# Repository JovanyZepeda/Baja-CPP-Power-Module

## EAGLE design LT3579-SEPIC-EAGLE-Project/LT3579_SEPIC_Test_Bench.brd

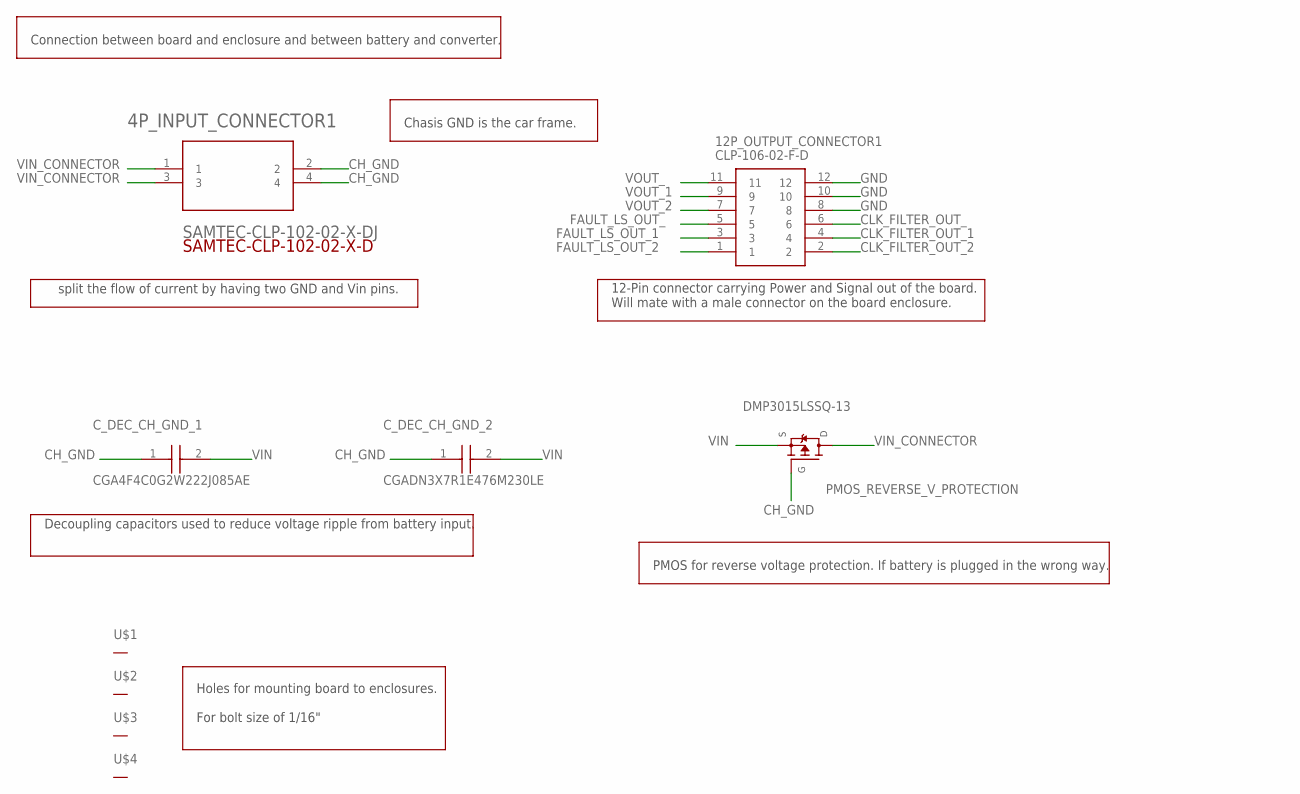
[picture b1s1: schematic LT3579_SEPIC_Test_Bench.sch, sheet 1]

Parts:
4P_INPUT_CONNECTOR1: SAMTEC-CLP-102-02-X-DJ; SAMTEC-CLP-102-02-X-D
12P_OUTPUT_CONNECTOR1: CLP-106-02-F-D; CLP-106-02-XXX
C_DEC_CH_GND_1: CGA4F4C0G2W222J085AE; CAPC2012X100N
C_DEC_CH_GND_2: CGADN3X7R1E476M230LE; CAPC7563X250N
PMOS_REVERSE_V_PROTECTION: DMP3015LSSQ-13; SOIC127P600X170-8N
U$1, U$2, U$3, U$4: THROUGH_HOLE_; THROUGH_HOLE

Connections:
CH_GND: 4P_INPUT_CONNECTOR1.2, 4P_INPUT_CONNECTOR1.4, C_DEC_CH_GND_1.1, C_DEC_CH_GND_2.1, PMOS_REVERSE_V_PROTECTION.4 (G1); also elsewhere on the board
CLK_FILTER_OUT_: 12P_OUTPUT_CONNECTOR1.6; also elsewhere on the board
CLK_FILTER_OUT_1: 12P_OUTPUT_CONNECTOR1.4; also elsewhere on the board
CLK_FILTER_OUT_2: 12P_OUTPUT_CONNECTOR1.2; also elsewhere on the board
FAULT_LS_OUT_: 12P_OUTPUT_CONNECTOR1.5; also elsewhere on the board
FAULT_LS_OUT_1: 12P_OUTPUT_CONNECTOR1.3; also elsewhere on the board
FAULT_LS_OUT_2: 12P_OUTPUT_CONNECTOR1.1; also elsewhere on the board
GND: 12P_OUTPUT_CONNECTOR1.8, 12P_OUTPUT_CONNECTOR1.10, 12P_OUTPUT_CONNECTOR1.12; also elsewhere on the board
VIN: C_DEC_CH_GND_1.2, C_DEC_CH_GND_2.2, PMOS_REVERSE_V_PROTECTION.1 (S1), PMOS_REVERSE_V_PROTECTION.2 (S1), PMOS_REVERSE_V_PROTECTION.3 (S1); also elsewhere on the board
VIN_CONNECTOR: 4P_INPUT_CONNECTOR1.1, 4P_INPUT_CONNECTOR1.3, PMOS_REVERSE_V_PROTECTION.5 (D1), PMOS_REVERSE_V_PROTECTION.6 (D1), PMOS_REVERSE_V_PROTECTION.7 (D1), PMOS_REVERSE_V_PROTECTION.8 (D1)
VOUT_: 12P_OUTPUT_CONNECTOR1.11; also elsewhere on the board
VOUT_1: 12P_OUTPUT_CONNECTOR1.9; also elsewhere on the board
VOUT_2: 12P_OUTPUT_CONNECTOR1.7; also elsewhere on the board

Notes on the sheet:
Connection between board and enclosure and between battery and converter.
split the flow of current by having two GND and Vin pins.
12-Pin connector carrying Power and Signal out of the board. Will mate with a male connector on the board enclosure.
Decoupling capacitors used to reduce voltage ripple from battery input.
PMOS for reverse voltage protection. If battery is plugged in the wrong way.
Chasis GND is the car frame.
Holes for mounting board to enclosures. For bolt size of 1/16"

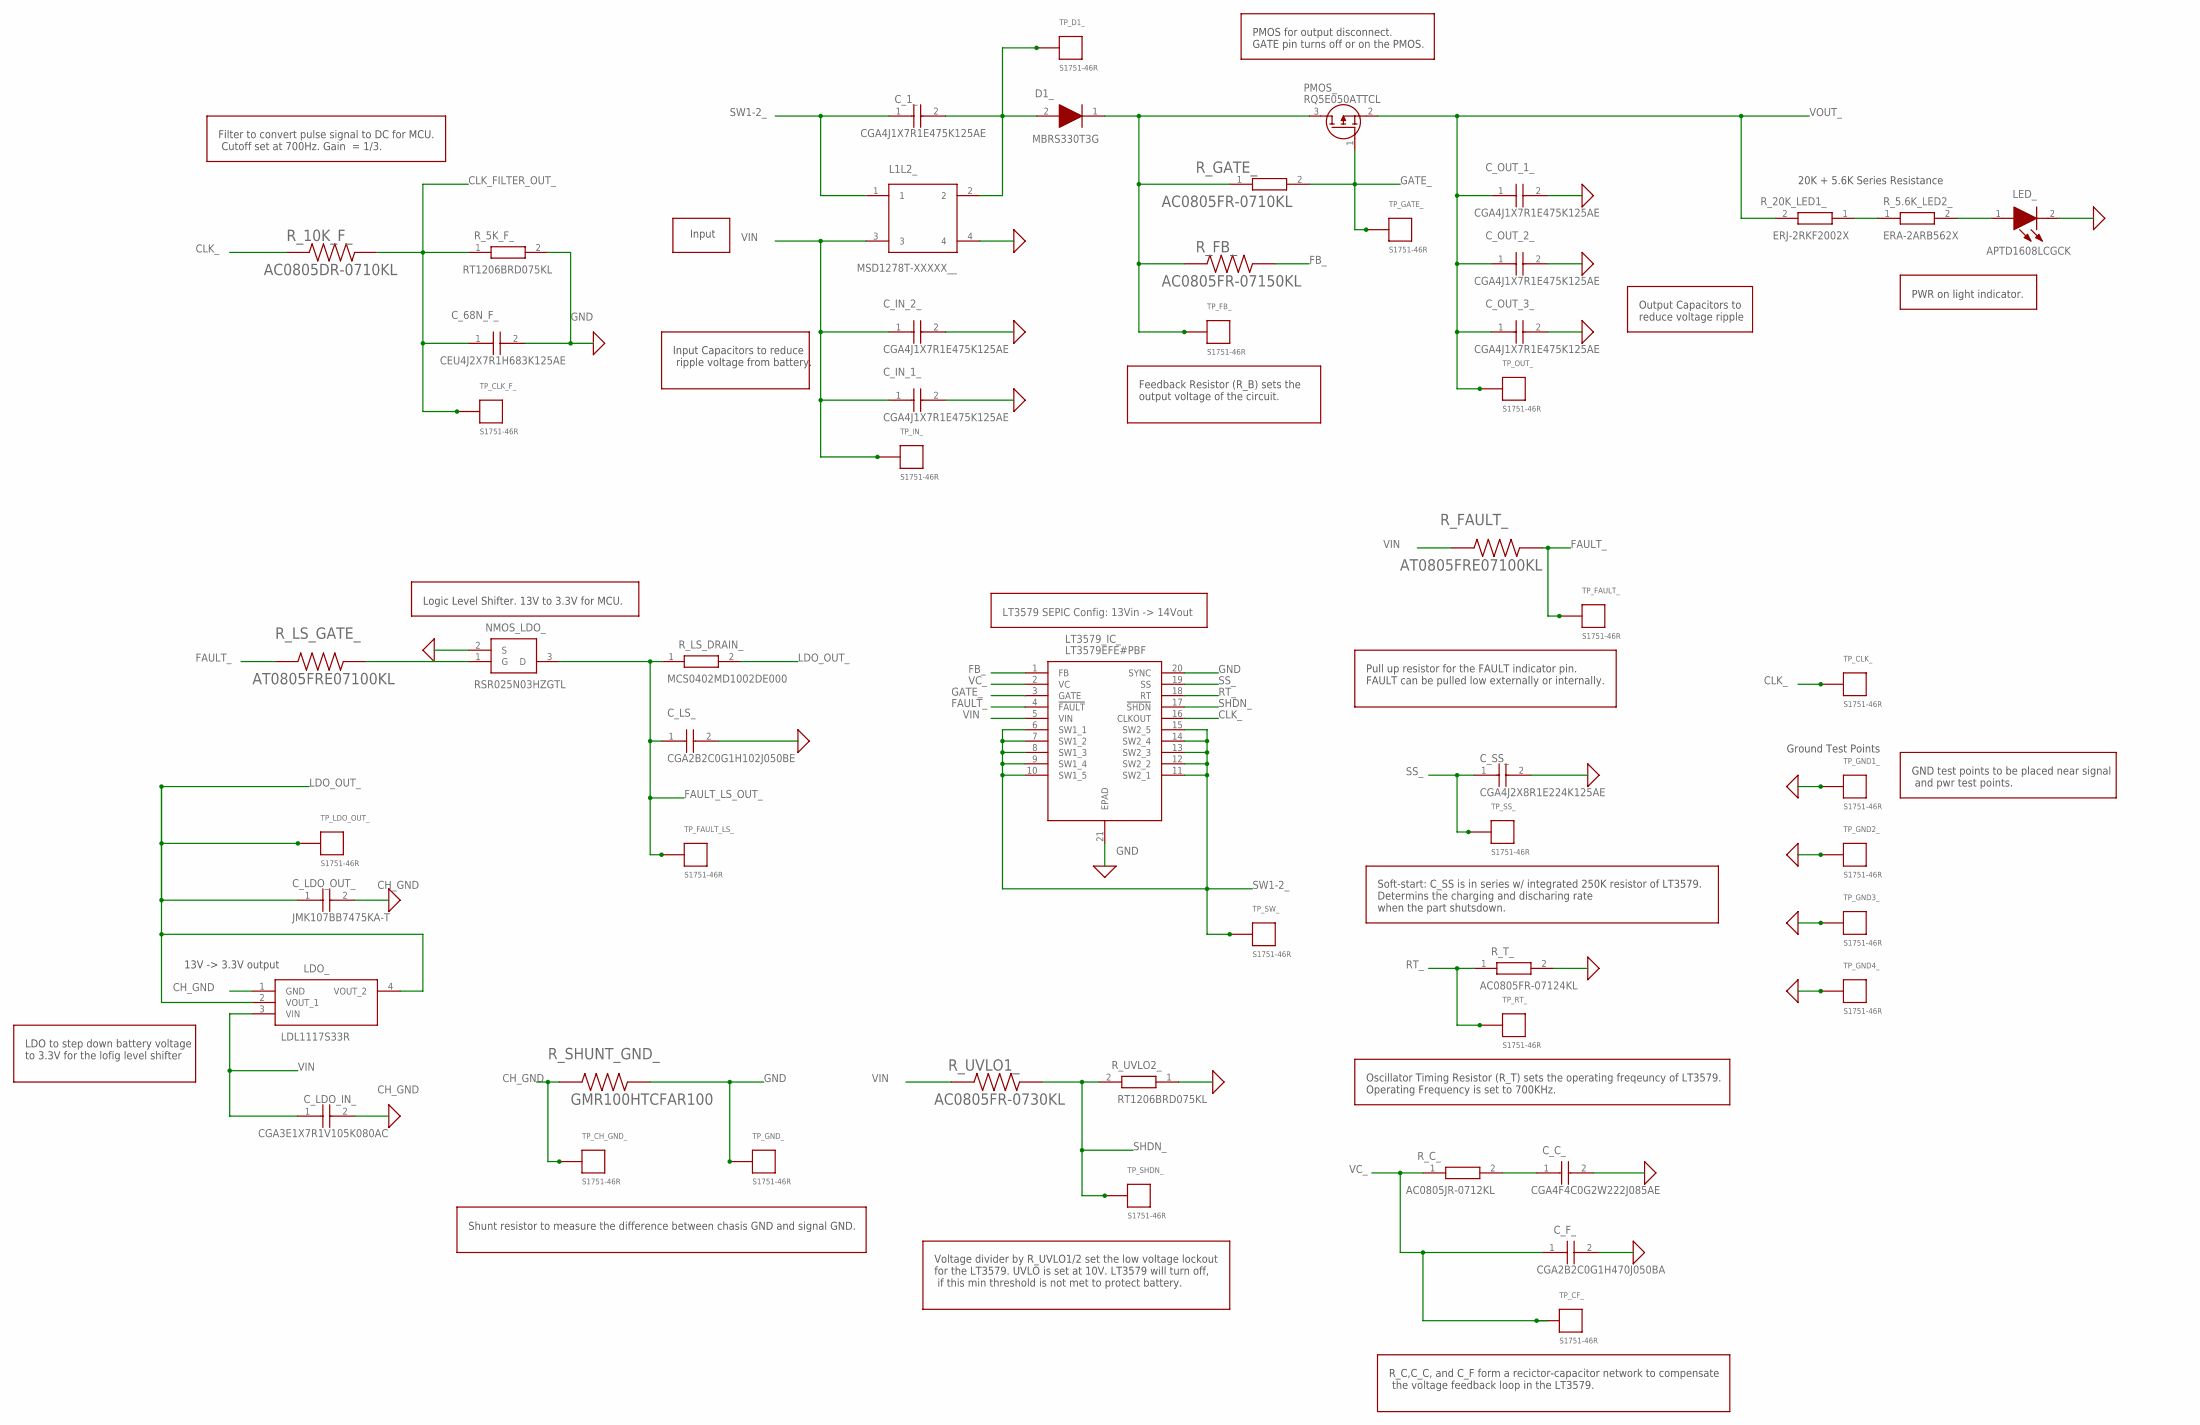
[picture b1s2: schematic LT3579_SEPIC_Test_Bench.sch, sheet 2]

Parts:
C_1_: CGA4J1X7R1E475K125AE; CAPC2012X145N
C_68N_F_: CEU4J2X7R1H683K125AE; CAPC2013X150N
C_C_: CGA4F4C0G2W222J085AE; CAPC2012X100N
C_F_: CGA2B2C0G1H470J050BA; CAPC1005X55N
C_IN_1_, C_IN_2_: CGA4J1X7R1E475K125AE; CAPC2012X145N
C_LDO_IN_: CGA3E1X7R1V105K080AC; CAPC1608X90N
C_LDO_OUT_: JMK107BB7475KA-T; CAPC1608X90N
C_LS_: CGA2B2C0G1H102J050BE; CAPC1005X55N
C_OUT_1_, C_OUT_2_, C_OUT_3_: CGA4J1X7R1E475K125AE; CAPC2012X145N
C_SS_: CGA4J2X8R1E224K125AE; CAPC2012X145N
D1_: MBRS330T3G; DIOM7958X256N
L1L2_: MSD1278T-XXXXX__; MSD1278T-822MLXX
LDO_: LDL1117S33R; SOT230P700X180-4N
LED_: APTD1608LCGCK; APT1608CGCK
LT3579_IC_: LT3579EFE#PBF; SOP65P640X120-21N
NMOS_LDO_: RSR025N03HZGTL; SOT95P280X100-3N
PMOS_: RQ5E050ATTCL; SOT95P280X100-3N
R_5.6K_LED2_: ERA-2ARB562X; ERA2AED122X
R_5K_F_: RT1206BRD075KL; RESC3116X65N
R_10K_F_: AC0805DR-0710KL; RESC2012X60N
R_20K_LED1_: ERJ-2RKF2002X; ERJ2R_(0402)
R_C_: AC0805JR-0712KL; RESC2012X60N
R_FAULT_: AT0805FRE07100KL; RESC2012X60N
R_FB_: AC0805FR-07150KL; RESC2012X60N
R_GATE_: AC0805FR-0710KL; RESC2012X60N
R_LS_DRAIN_: MCS0402MD1002DE000; RESC1005X37N
R_LS_GATE_: AT0805FRE07100KL; RESC2012X60N
R_SHUNT_GND_: GMR100HTCFAR100; RESC6432X55N
R_T_: AC0805FR-07124KL; RESC2012X60N
R_UVLO1_: AC0805FR-0730KL; RESC2012X60N
R_UVLO2_: RT1206BRD075KL; RESC3116X65N
TP_CF_: S1751-46R; S1751-46R_
TP_CH_GND_: S1751-46R; S1751-46R_
TP_CLK_: S1751-46R; S1751-46R_
TP_CLK_F_: S1751-46R; S1751-46R_
TP_D1_: S1751-46R; S1751-46R_
TP_FAULT_: S1751-46R; S1751-46R_
TP_FAULT_LS_: S1751-46R; S1751-46R_
TP_FB_: S1751-46R; S1751-46R_
TP_GATE_: S1751-46R; S1751-46R_
TP_GND1_, TP_GND2_, TP_GND3_, TP_GND4_: S1751-46R; S1751-46R_
TP_GND_: S1751-46R; S1751-46R_
TP_IN_: S1751-46R; S1751-46R_
TP_LDO_OUT_: S1751-46R; S1751-46R_
TP_OUT_: S1751-46R; S1751-46R_
TP_RT_: S1751-46R; S1751-46R_
TP_SHDN_: S1751-46R; S1751-46R_
TP_SS_: S1751-46R; S1751-46R_
TP_SW_: S1751-46R; S1751-46R_

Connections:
CH_GND: C_LDO_IN_.2, C_LDO_OUT_.2, LDO_.1 (GND), R_SHUNT_GND_.1, TP_CH_GND_.1; also elsewhere on the board
CLK_: LT3579_IC_.16 (CLKOUT), R_10K_F_.1, TP_CLK_.1
CLK_FILTER_OUT_: C_68N_F_.1, R_5K_F_.1, R_10K_F_.2, TP_CLK_F_.1; also elsewhere on the board
FAULT_: LT3579_IC_.4 (!FAULT), R_FAULT_.1, R_LS_GATE_.1, TP_FAULT_.1
FAULT_LS_OUT_: C_LS_.1, NMOS_LDO_.3 (D), R_LS_DRAIN_.1, TP_FAULT_LS_.1; also elsewhere on the board
FB_: LT3579_IC_.1 (FB), R_FB_.2
GATE_: LT3579_IC_.3 (GATE), PMOS_.1 (G), R_GATE_.2, TP_GATE_.1
GND: C_68N_F_.2, C_C_.2, C_F_.2, C_IN_1_.2, C_IN_2_.2, C_LS_.2, C_OUT_1_.2, C_OUT_2_.2, C_OUT_3_.2, C_SS_.2, L1L2_.4, LED_.2 (K), LT3579_IC_.20 (SYNC), LT3579_IC_.21 (EPAD), NMOS_LDO_.2 (S), R_5K_F_.2, R_SHUNT_GND_.2, R_T_.2, R_UVLO2_.1, TP_GND1_.1, TP_GND2_.1, TP_GND3_.1, TP_GND4_.1, TP_GND_.1; also elsewhere on the board
LDO_OUT_: C_LDO_OUT_.1, LDO_.2 (VOUT_1), LDO_.4 (VOUT_2), R_LS_DRAIN_.2, TP_LDO_OUT_.1; also elsewhere on the board
unnamed: C_C_.1, R_C_.2
unnamed: NMOS_LDO_.1 (G), R_LS_GATE_.2
unnamed: C_1_.2, D1_.2 (A), L1L2_.2, TP_D1_.1
unnamed: R_5.6K_LED2_.1, R_20K_LED1_.1
unnamed: D1_.1 (K), PMOS_.3 (D), R_FB_.1, R_GATE_.1, TP_FB_.1
unnamed: LED_.1 (A), R_5.6K_LED2_.2
RT_: LT3579_IC_.18 (RT), R_T_.1, TP_RT_.1
SHDN_: LT3579_IC_.17 (!SHDN), R_UVLO1_.1, R_UVLO2_.2, TP_SHDN_.1
SS_: C_SS_.1, LT3579_IC_.19 (SS), TP_SS_.1
SW1-2_: C_1_.1, L1L2_.1, LT3579_IC_.6 (SW1_1), LT3579_IC_.7 (SW1_2), LT3579_IC_.8 (SW1_3), LT3579_IC_.9 (SW1_4), LT3579_IC_.10 (SW1_5), LT3579_IC_.11 (SW2_1), LT3579_IC_.12 (SW2_2), LT3579_IC_.13 (SW2_3), LT3579_IC_.14 (SW2_4), LT3579_IC_.15 (SW2_5), TP_SW_.1
VC_: C_F_.1, LT3579_IC_.2 (VC), R_C_.1, TP_CF_.1
VIN: C_IN_1_.1, C_IN_2_.1, C_LDO_IN_.1, L1L2_.3, LDO_.3 (VIN), LT3579_IC_.5 (VIN), R_FAULT_.2, R_UVLO1_.2, TP_IN_.1; also elsewhere on the board
VOUT_: C_OUT_1_.1, C_OUT_2_.1, C_OUT_3_.1, PMOS_.2 (S), R_20K_LED1_.2, TP_OUT_.1; also elsewhere on the board

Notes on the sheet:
LT3579 SEPIC Config: 13Vin -> 14Vout
Ground Test Points
Filter to convert pulse signal to DC for MCU. Cutoff set at 700Hz. Gain = 1/3.
13V -> 3.3V output
Logic Level Shifter. 13V to 3.3V for MCU.
20K + 5.6K Series Resistance
PWR on light indicator.
Voltage divider by R_UVLO1/2 set the low voltage lockout for the LT3579. UVLO is set at 10V. LT3579 will turn off, if this min threshold is not met to protect battery.
Oscillator Timing Resistor (R_T) sets the operating freqeuncy of LT3579. Operating Frequency is set to 700KHz.
R_C,C_C, and C_F form a recictor-capacitor network to compensate the voltage feedback loop in the LT3579.
Soft-start: C_SS is in series w/ integrated 250K resistor of LT3579. Determins the charging and discharing rate when the part shutsdown.
Pull up resistor for the FAULT indicator pin. FAULT can be pulled low externally or internally.
Shunt resistor to measure the difference between chasis GND and signal GND.
LDO to step down battery voltage to 3.3V for the lofig level shifter
GND test points to be placed near signal and pwr test points.
Input Capacitors to reduce ripple voltage from battery.
Output Capacitors to reduce voltage ripple
PMOS for output disconnect. GATE pin turns off or on the PMOS.
Feedback Resistor (R_B) sets the output voltage of the circuit.
Input

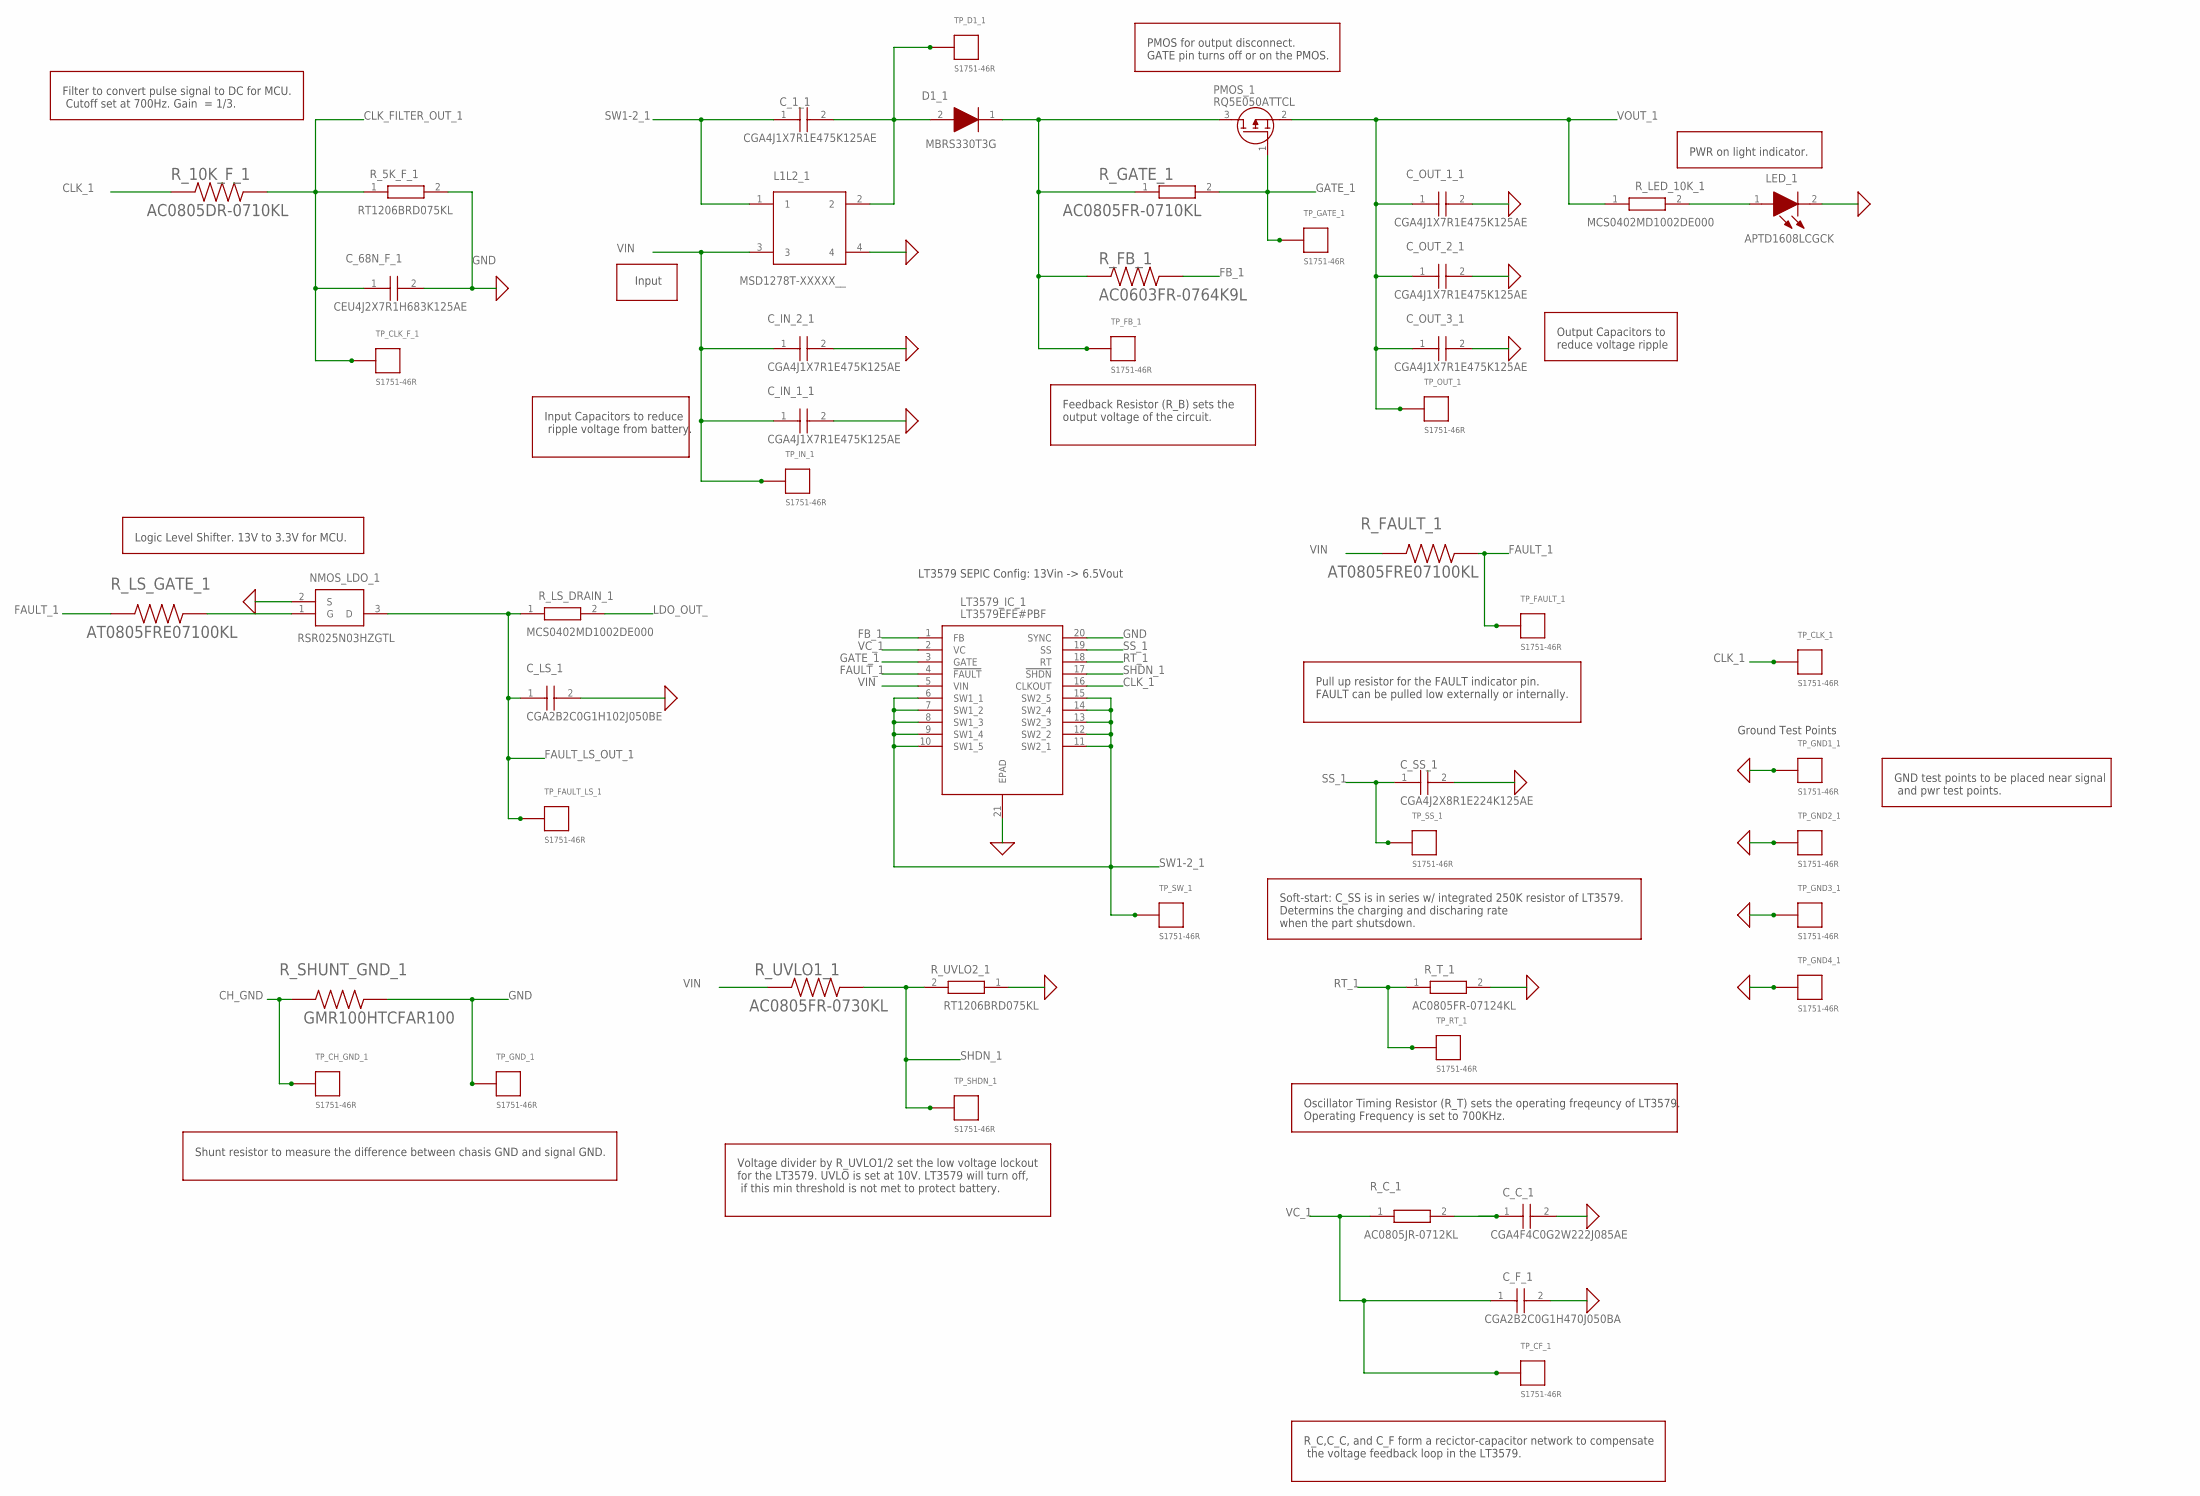
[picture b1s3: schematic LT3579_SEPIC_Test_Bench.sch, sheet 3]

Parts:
C_1_1: CGA4J1X7R1E475K125AE; CAPC2012X145N
C_68N_F_1: CEU4J2X7R1H683K125AE; CAPC2013X150N
C_C_1: CGA4F4C0G2W222J085AE; CAPC2012X100N
C_F_1: CGA2B2C0G1H470J050BA; CAPC1005X55N
C_IN_1_1, C_IN_2_1: CGA4J1X7R1E475K125AE; CAPC2012X145N
C_LS_1: CGA2B2C0G1H102J050BE; CAPC1005X55N
C_OUT_1_1, C_OUT_2_1, C_OUT_3_1: CGA4J1X7R1E475K125AE; CAPC2012X145N
C_SS_1: CGA4J2X8R1E224K125AE; CAPC2012X145N
D1_1: MBRS330T3G; DIOM7958X256N
L1L2_1: MSD1278T-XXXXX__; MSD1278T-822MLXX
LED_1: APTD1608LCGCK; APT1608CGCK
LT3579_IC_1: LT3579EFE#PBF; SOP65P640X120-21N
NMOS_LDO_1: RSR025N03HZGTL; SOT95P280X100-3N
PMOS_1: RQ5E050ATTCL; SOT95P280X100-3N
R_5K_F_1: RT1206BRD075KL; RESC3116X65N
R_10K_F_1: AC0805DR-0710KL; RESC2012X60N
R_C_1: AC0805JR-0712KL; RESC2012X60N
R_FAULT_1: AT0805FRE07100KL; RESC2012X60N
R_FB_1: AC0603FR-0764K9L; RESC1608X55N
R_GATE_1: AC0805FR-0710KL; RESC2012X60N
R_LED_10K_1: MCS0402MD1002DE000; RESC1005X37N
R_LS_DRAIN_1: MCS0402MD1002DE000; RESC1005X37N
R_LS_GATE_1: AT0805FRE07100KL; RESC2012X60N
R_SHUNT_GND_1: GMR100HTCFAR100; RESC6432X55N
R_T_1: AC0805FR-07124KL; RESC2012X60N
R_UVLO1_1: AC0805FR-0730KL; RESC2012X60N
R_UVLO2_1: RT1206BRD075KL; RESC3116X65N
TP_CF_1: S1751-46R; S1751-46R_
TP_CH_GND_1: S1751-46R; S1751-46R_
TP_CLK_1: S1751-46R; S1751-46R_
TP_CLK_F_1: S1751-46R; S1751-46R_
TP_D1_1: S1751-46R; S1751-46R_
TP_FAULT_1: S1751-46R; S1751-46R_
TP_FAULT_LS_1: S1751-46R; S1751-46R_
TP_FB_1: S1751-46R; S1751-46R_
TP_GATE_1: S1751-46R; S1751-46R_
TP_GND1_1, TP_GND2_1, TP_GND3_1, TP_GND4_1: S1751-46R; S1751-46R_
TP_GND_1: S1751-46R; S1751-46R_
TP_IN_1: S1751-46R; S1751-46R_
TP_OUT_1: S1751-46R; S1751-46R_
TP_RT_1: S1751-46R; S1751-46R_
TP_SHDN_1: S1751-46R; S1751-46R_
TP_SS_1: S1751-46R; S1751-46R_
TP_SW_1: S1751-46R; S1751-46R_

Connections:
CH_GND: R_SHUNT_GND_1.1, TP_CH_GND_1.1; also elsewhere on the board
CLK_1: LT3579_IC_1.16 (CLKOUT), R_10K_F_1.1, TP_CLK_1.1
CLK_FILTER_OUT_1: C_68N_F_1.1, R_5K_F_1.1, R_10K_F_1.2, TP_CLK_F_1.1; also elsewhere on the board
FAULT_1: LT3579_IC_1.4 (!FAULT), R_FAULT_1.1, R_LS_GATE_1.1, TP_FAULT_1.1
FAULT_LS_OUT_1: C_LS_1.1, NMOS_LDO_1.3 (D), R_LS_DRAIN_1.1, TP_FAULT_LS_1.1; also elsewhere on the board
FB_1: LT3579_IC_1.1 (FB), R_FB_1.2
GATE_1: LT3579_IC_1.3 (GATE), PMOS_1.1 (G), R_GATE_1.2, TP_GATE_1.1
GND: C_68N_F_1.2, C_C_1.2, C_F_1.2, C_IN_1_1.2, C_IN_2_1.2, C_LS_1.2, C_OUT_1_1.2, C_OUT_2_1.2, C_OUT_3_1.2, C_SS_1.2, L1L2_1.4, LED_1.2 (K), LT3579_IC_1.20 (SYNC), LT3579_IC_1.21 (EPAD), NMOS_LDO_1.2 (S), R_5K_F_1.2, R_SHUNT_GND_1.2, R_T_1.2, R_UVLO2_1.1, TP_GND1_1.1, TP_GND2_1.1, TP_GND3_1.1, TP_GND4_1.1, TP_GND_1.1; also elsewhere on the board
LDO_OUT_: R_LS_DRAIN_1.2; also elsewhere on the board
unnamed: C_1_1.2, D1_1.2 (A), L1L2_1.2, TP_D1_1.1
unnamed: C_C_1.1, R_C_1.2
unnamed: D1_1.1 (K), PMOS_1.3 (D), R_FB_1.1, R_GATE_1.1, TP_FB_1.1
unnamed: NMOS_LDO_1.1 (G), R_LS_GATE_1.2
unnamed: LED_1.1 (A), R_LED_10K_1.2
RT_1: LT3579_IC_1.18 (RT), R_T_1.1, TP_RT_1.1
SHDN_1: LT3579_IC_1.17 (!SHDN), R_UVLO1_1.1, R_UVLO2_1.2, TP_SHDN_1.1
SS_1: C_SS_1.1, LT3579_IC_1.19 (SS), TP_SS_1.1
SW1-2_1: C_1_1.1, L1L2_1.1, LT3579_IC_1.6 (SW1_1), LT3579_IC_1.7 (SW1_2), LT3579_IC_1.8 (SW1_3), LT3579_IC_1.9 (SW1_4), LT3579_IC_1.10 (SW1_5), LT3579_IC_1.11 (SW2_1), LT3579_IC_1.12 (SW2_2), LT3579_IC_1.13 (SW2_3), LT3579_IC_1.14 (SW2_4), LT3579_IC_1.15 (SW2_5), TP_SW_1.1
VC_1: C_F_1.1, LT3579_IC_1.2 (VC), R_C_1.1, TP_CF_1.1
VIN: C_IN_1_1.1, C_IN_2_1.1, L1L2_1.3, LT3579_IC_1.5 (VIN), R_FAULT_1.2, R_UVLO1_1.2, TP_IN_1.1; also elsewhere on the board
VOUT_1: C_OUT_1_1.1, C_OUT_2_1.1, C_OUT_3_1.1, PMOS_1.2 (S), R_LED_10K_1.1, TP_OUT_1.1; also elsewhere on the board

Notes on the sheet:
LT3579 SEPIC Config: 13Vin -> 6.5Vout
Ground Test Points
Filter to convert pulse signal to DC for MCU. Cutoff set at 700Hz. Gain = 1/3.
Logic Level Shifter. 13V to 3.3V for MCU.
Voltage divider by R_UVLO1/2 set the low voltage lockout for the LT3579. UVLO is set at 10V. LT3579 will turn off, if this min threshold is not met to protect battery.
R_C,C_C, and C_F form a recictor-capacitor network to compensate the voltage feedback loop in the LT3579.
Oscillator Timing Resistor (R_T) sets the operating freqeuncy of LT3579. Operating Frequency is set to 700KHz.
Soft-start: C_SS is in series w/ integrated 250K resistor of LT3579. Determins the charging and discharing rate when the part shutsdown.
GND test points to be placed near signal and pwr test points.
Pull up resistor for the FAULT indicator pin. FAULT can be pulled low externally or internally.
PWR on light indicator.
Output Capacitors to reduce voltage ripple
Feedback Resistor (R_B) sets the output voltage of the circuit.
PMOS for output disconnect. GATE pin turns off or on the PMOS.
Input Capacitors to reduce ripple voltage from battery.
Input
Shunt resistor to measure the difference between chasis GND and signal GND.

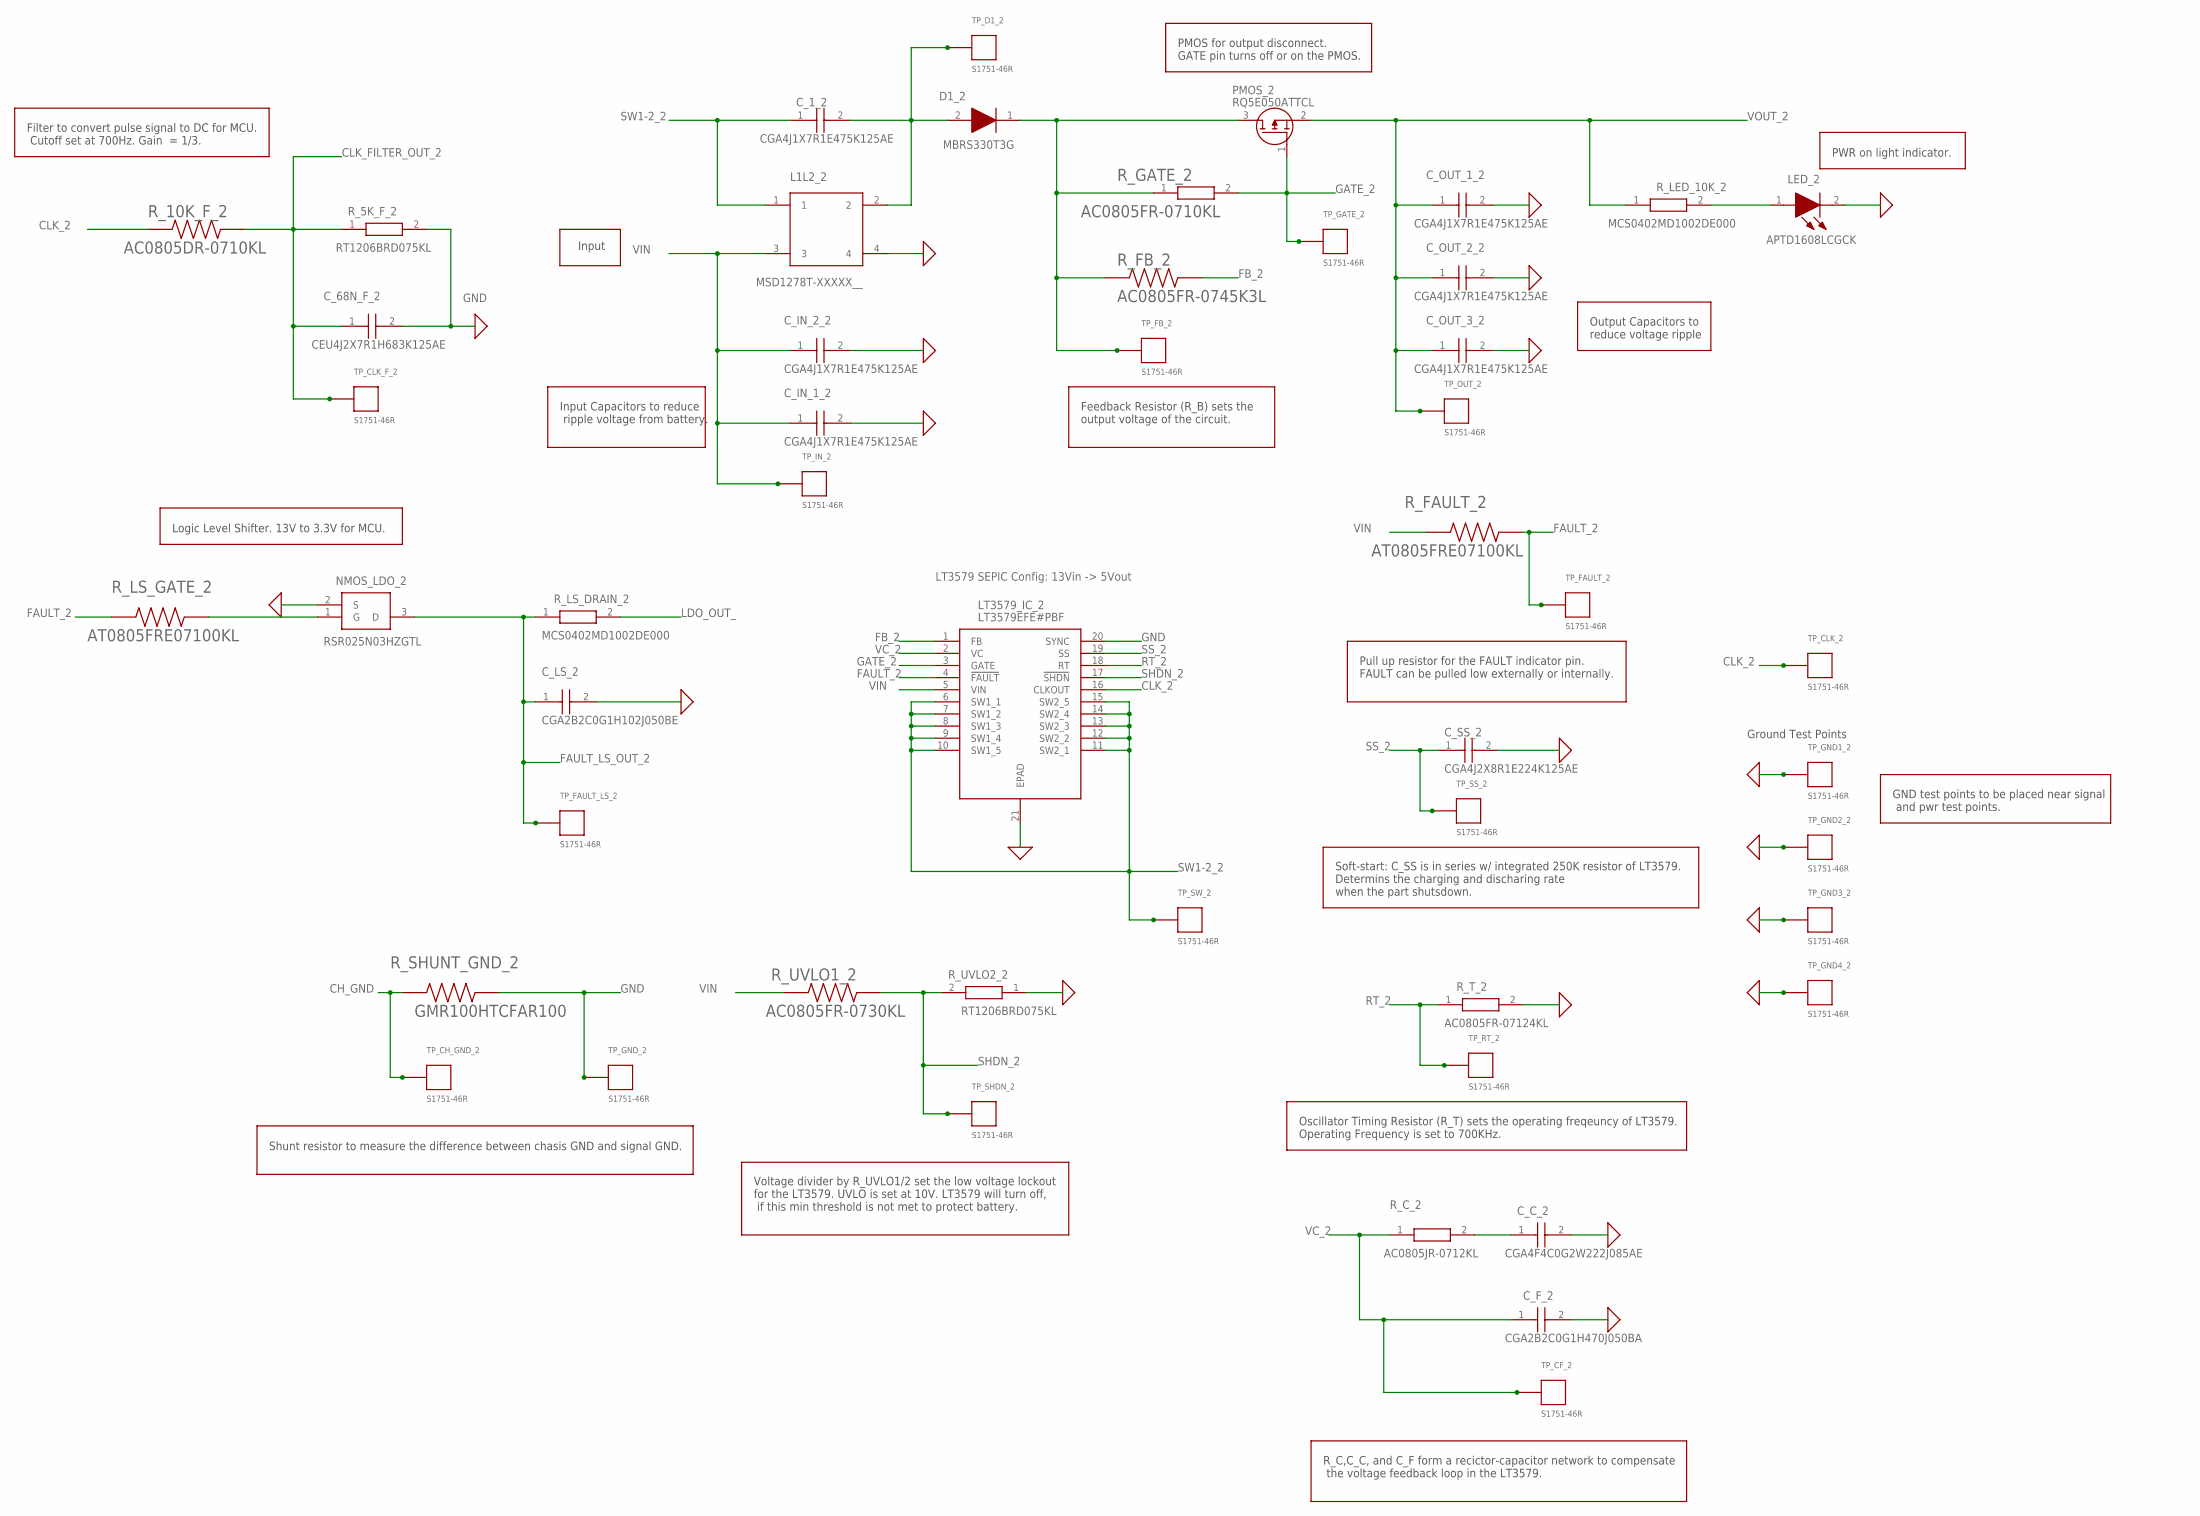
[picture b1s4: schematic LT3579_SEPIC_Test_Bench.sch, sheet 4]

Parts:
C_1_2: CGA4J1X7R1E475K125AE; CAPC2012X145N
C_68N_F_2: CEU4J2X7R1H683K125AE; CAPC2013X150N
C_C_2: CGA4F4C0G2W222J085AE; CAPC2012X100N
C_F_2: CGA2B2C0G1H470J050BA; CAPC1005X55N
C_IN_1_2, C_IN_2_2: CGA4J1X7R1E475K125AE; CAPC2012X145N
C_LS_2: CGA2B2C0G1H102J050BE; CAPC1005X55N
C_OUT_1_2, C_OUT_2_2, C_OUT_3_2: CGA4J1X7R1E475K125AE; CAPC2012X145N
C_SS_2: CGA4J2X8R1E224K125AE; CAPC2012X145N
D1_2: MBRS330T3G; DIOM7958X256N
L1L2_2: MSD1278T-XXXXX__; MSD1278T-822MLXX
LED_2: APTD1608LCGCK; APT1608CGCK
LT3579_IC_2: LT3579EFE#PBF; SOP65P640X120-21N
NMOS_LDO_2: RSR025N03HZGTL; SOT95P280X100-3N
PMOS_2: RQ5E050ATTCL; SOT95P280X100-3N
R_5K_F_2: RT1206BRD075KL; RESC3116X65N
R_10K_F_2: AC0805DR-0710KL; RESC2012X60N
R_C_2: AC0805JR-0712KL; RESC2012X60N
R_FAULT_2: AT0805FRE07100KL; RESC2012X60N
R_FB_2: AC0805FR-0745K3L; RESC2012X60N
R_GATE_2: AC0805FR-0710KL; RESC2012X60N
R_LED_10K_2: MCS0402MD1002DE000; RESC1005X37N
R_LS_DRAIN_2: MCS0402MD1002DE000; RESC1005X37N
R_LS_GATE_2: AT0805FRE07100KL; RESC2012X60N
R_SHUNT_GND_2: GMR100HTCFAR100; RESC6432X55N
R_T_2: AC0805FR-07124KL; RESC2012X60N
R_UVLO1_2: AC0805FR-0730KL; RESC2012X60N
R_UVLO2_2: RT1206BRD075KL; RESC3116X65N
TP_CF_2: S1751-46R; S1751-46R_
TP_CH_GND_2: S1751-46R; S1751-46R_
TP_CLK_2: S1751-46R; S1751-46R_
TP_CLK_F_2: S1751-46R; S1751-46R_
TP_D1_2: S1751-46R; S1751-46R_
TP_FAULT_2: S1751-46R; S1751-46R_
TP_FAULT_LS_2: S1751-46R; S1751-46R_
TP_FB_2: S1751-46R; S1751-46R_
TP_GATE_2: S1751-46R; S1751-46R_
TP_GND1_2, TP_GND2_2, TP_GND3_2, TP_GND4_2: S1751-46R; S1751-46R_
TP_GND_2: S1751-46R; S1751-46R_
TP_IN_2: S1751-46R; S1751-46R_
TP_OUT_2: S1751-46R; S1751-46R_
TP_RT_2: S1751-46R; S1751-46R_
TP_SHDN_2: S1751-46R; S1751-46R_
TP_SS_2: S1751-46R; S1751-46R_
TP_SW_2: S1751-46R; S1751-46R_

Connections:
CH_GND: R_SHUNT_GND_2.1, TP_CH_GND_2.1; also elsewhere on the board
CLK_2: LT3579_IC_2.16 (CLKOUT), R_10K_F_2.1, TP_CLK_2.1
CLK_FILTER_OUT_2: C_68N_F_2.1, R_5K_F_2.1, R_10K_F_2.2, TP_CLK_F_2.1; also elsewhere on the board
FAULT_2: LT3579_IC_2.4 (!FAULT), R_FAULT_2.1, R_LS_GATE_2.1, TP_FAULT_2.1
FAULT_LS_OUT_2: C_LS_2.1, NMOS_LDO_2.3 (D), R_LS_DRAIN_2.1, TP_FAULT_LS_2.1; also elsewhere on the board
FB_2: LT3579_IC_2.1 (FB), R_FB_2.2
GATE_2: LT3579_IC_2.3 (GATE), PMOS_2.1 (G), R_GATE_2.2, TP_GATE_2.1
GND: C_68N_F_2.2, C_C_2.2, C_F_2.2, C_IN_1_2.2, C_IN_2_2.2, C_LS_2.2, C_OUT_1_2.2, C_OUT_2_2.2, C_OUT_3_2.2, C_SS_2.2, L1L2_2.4, LED_2.2 (K), LT3579_IC_2.20 (SYNC), LT3579_IC_2.21 (EPAD), NMOS_LDO_2.2 (S), R_5K_F_2.2, R_SHUNT_GND_2.2, R_T_2.2, R_UVLO2_2.1, TP_GND1_2.1, TP_GND2_2.1, TP_GND3_2.1, TP_GND4_2.1, TP_GND_2.1; also elsewhere on the board
LDO_OUT_: R_LS_DRAIN_2.2; also elsewhere on the board
unnamed: C_1_2.2, D1_2.2 (A), L1L2_2.2, TP_D1_2.1
unnamed: C_C_2.1, R_C_2.2
unnamed: D1_2.1 (K), PMOS_2.3 (D), R_FB_2.1, R_GATE_2.1, TP_FB_2.1
unnamed: NMOS_LDO_2.1 (G), R_LS_GATE_2.2
unnamed: LED_2.1 (A), R_LED_10K_2.2
RT_2: LT3579_IC_2.18 (RT), R_T_2.1, TP_RT_2.1
SHDN_2: LT3579_IC_2.17 (!SHDN), R_UVLO1_2.1, R_UVLO2_2.2, TP_SHDN_2.1
SS_2: C_SS_2.1, LT3579_IC_2.19 (SS), TP_SS_2.1
SW1-2_2: C_1_2.1, L1L2_2.1, LT3579_IC_2.6 (SW1_1), LT3579_IC_2.7 (SW1_2), LT3579_IC_2.8 (SW1_3), LT3579_IC_2.9 (SW1_4), LT3579_IC_2.10 (SW1_5), LT3579_IC_2.11 (SW2_1), LT3579_IC_2.12 (SW2_2), LT3579_IC_2.13 (SW2_3), LT3579_IC_2.14 (SW2_4), LT3579_IC_2.15 (SW2_5), TP_SW_2.1
VC_2: C_F_2.1, LT3579_IC_2.2 (VC), R_C_2.1, TP_CF_2.1
VIN: C_IN_1_2.1, C_IN_2_2.1, L1L2_2.3, LT3579_IC_2.5 (VIN), R_FAULT_2.2, R_UVLO1_2.2, TP_IN_2.1; also elsewhere on the board
VOUT_2: C_OUT_1_2.1, C_OUT_2_2.1, C_OUT_3_2.1, PMOS_2.2 (S), R_LED_10K_2.1, TP_OUT_2.1; also elsewhere on the board

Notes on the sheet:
LT3579 SEPIC Config: 13Vin -> 5Vout
Ground Test Points
Filter to convert pulse signal to DC for MCU. Cutoff set at 700Hz. Gain = 1/3.
Logic Level Shifter. 13V to 3.3V for MCU.
Voltage divider by R_UVLO1/2 set the low voltage lockout for the LT3579. UVLO is set at 10V. LT3579 will turn off, if this min threshold is not met to protect battery.
R_C,C_C, and C_F form a recictor-capacitor network to compensate the voltage feedback loop in the LT3579.
Oscillator Timing Resistor (R_T) sets the operating freqeuncy of LT3579. Operating Frequency is set to 700KHz.
Soft-start: C_SS is in series w/ integrated 250K resistor of LT3579. Determins the charging and discharing rate when the part shutsdown.
GND test points to be placed near signal and pwr test points.
Pull up resistor for the FAULT indicator pin. FAULT can be pulled low externally or internally.
PWR on light indicator.
Output Capacitors to reduce voltage ripple
Feedback Resistor (R_B) sets the output voltage of the circuit.
PMOS for output disconnect. GATE pin turns off or on the PMOS.
Input Capacitors to reduce ripple voltage from battery.
Input
Shunt resistor to measure the difference between chasis GND and signal GND.
